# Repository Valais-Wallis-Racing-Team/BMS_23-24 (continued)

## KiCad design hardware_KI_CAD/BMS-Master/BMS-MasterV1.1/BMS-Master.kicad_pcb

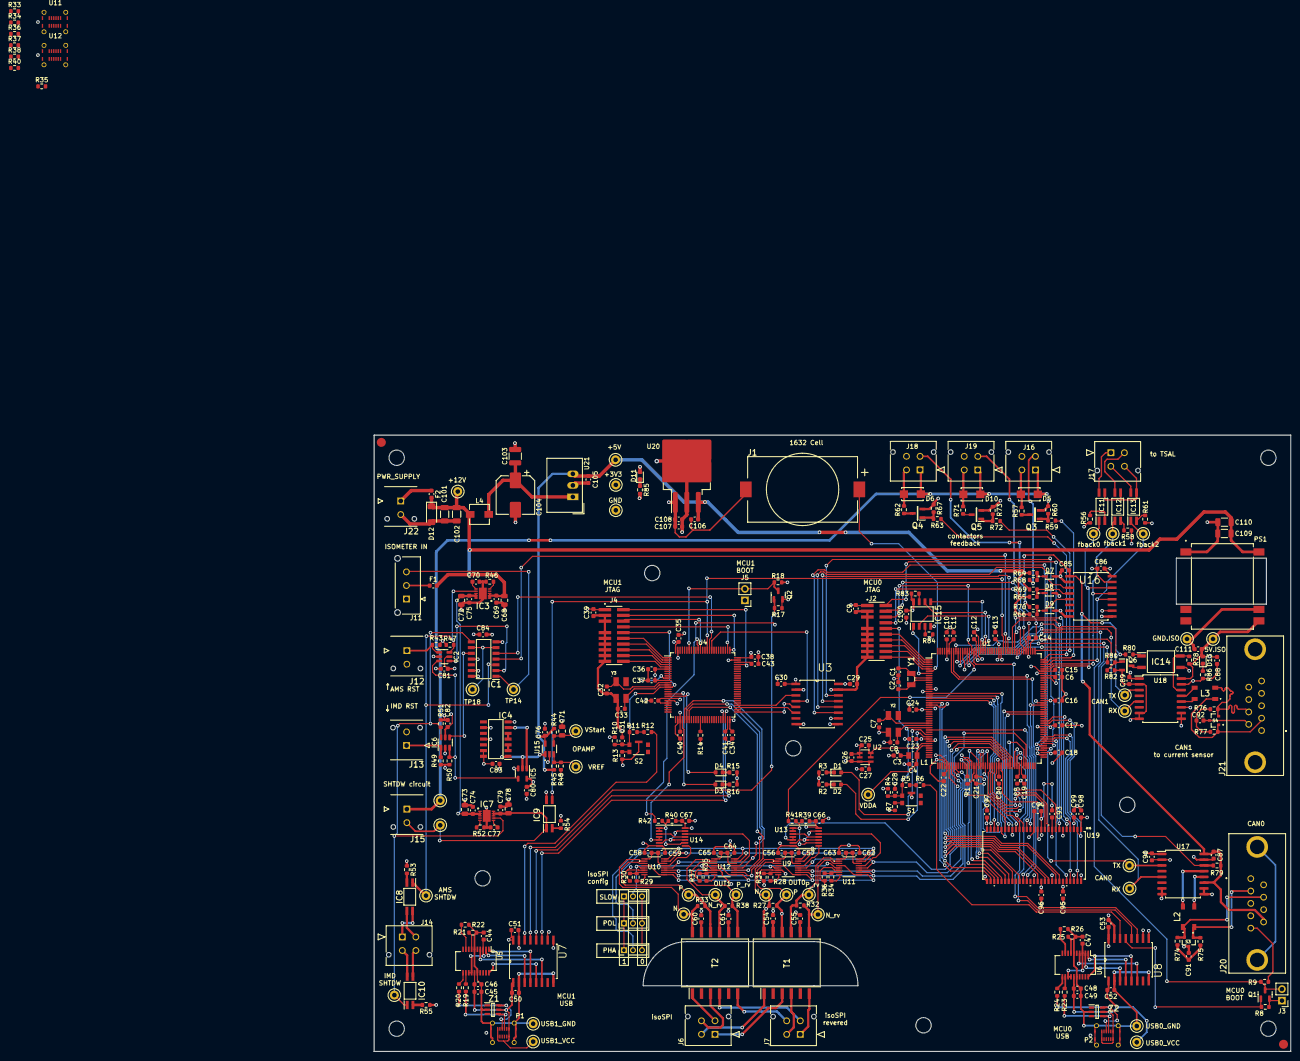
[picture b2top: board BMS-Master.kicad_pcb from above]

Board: 4 copper layers, 202.7 x 136.3 mm, 339 parts (0 on the bottom side), 274 nets.

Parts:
C1, C2, C7, C8, C32, C33: 18pF/50V; C_0603_1608Metric
C3, C4, C9, C10, C11, C12, C13, C14, C15, C16, C17, C18, C19, C20, C21, C22, C23, C24, C25, C27, C28, C29, C30, C31, C34, C35, C36, C37, C38, C39, C40, C42, C70, C77, C85, C86, C87, C88, C89, C90, C105, C106, C108, C111: 100nF/50V; C_0603_1608Metric
C5, C6, C41, C43: 2u2/10V; C_0603_1608Metric
C26, C91, C92, C107: 1uF/35V; C_0603_1608Metric
C44, C46, C47, C49, C50, C51, C52, C53, C56, C57, C58, C59, C62, C63, C64, C65, C66, C67, C76, C80, C81, C82, C83, C84, C93, C94, C95, C96, C97, C98, C99, C100: 100n/50V; C_0603_1608Metric
C45, C48: 4u7/25V; C_0603_1608Metric
C54, C55, C60, C61: 27pF/50V; C_0603_1608Metric
C68, C72, C73, C78: 10u/50V; C_0805_2012Metric
C69, C74, C75, C79: 0.1u/50V; C_0603_1608Metric
C71: 6.8uF/50V; C_0805_2012Metric
C101, C102: 10uF/50V; C_1206_3216Metric
C103: 10uF/50V; C_1210_3225Metric
C104: 56uF/50V; CP_Elec_8x10
C109, C110: 47uF/25V; C_1206_3216Metric
D1, D3: LED_RED; LED_0603_1608Metric
D2, D4: LED_Green; LED_0603_1608Metric
D5, D6, D10: GF1B-E3_67A; Diode_GF1B-E367A
D7, D8, D9: CDSOD323-T05; Bourns_Inc.-SOD-323-0-0-IPC_B
D11, D13: LED orange; LED_0603_1608Metric
D12: BZV55B15; D_MiniMELF
F1: 0408002.WR; Fuse_0603_1608Metric
F2: 0408007.WR; Fuse_0603_1608Metric
FID1, FID2: Fiducial; fiducial 2mm with 3mm mask
IC1: SN74LVC08AD; SOIC127P600X175-14N
IC2, IC6: SN74LVC1G332DBVR; TSOT-23-6
IC3, IC7: LS1205EF; SON50P300X300X80-11N
IC4: SN74HC04DR; SOIC127P600X175-14N
IC5: SN74LVC1G02DBVT; TSOT-23-5
IC8, IC9, IC10, IC11, IC12, IC13: ACPL-217-56BE; SOIC127P700X242-4N
IC14: AQY-211EHA; SOP254P962X315-4N
IC15: M95M02-DRMN6TP; SOIC127P600X175-8N
J1: SMTU1632-LF.TR; SMTU1632LFTR
J2, J4: FTSH-110-01-L-DV-007; SAMTEC_FTSH-110-01-L-DV-007
J3, J5: Conn_01x02_Pin; PinHeader_1x02_P2.54mm_Vertical
J6, J7, J14, J16, J17, J18, J19: 430450412; CON_430450412_MOL
J8, J9, J10: Conn_01x03_Pin; PinHeader_1x03_P2.00mm_Vertical
J11: 436500327; MOLEX_436500327
J12, J13, J15, J22: 43045-0212; 43045-02YY_121314
J20, J21: DE9_Receptacle_MountingHoles; L177TSEH09SOL2RM8
L1: BLM21AG471SN1J; IND_BLM21_0805_MUR
L2, L3: ACT45B 2000uH; ACT45B1012PTL003
L4: 5.6uH; L_TracoPower_TCK-141
P1, P2: USB_C_Plug_USB2.0; molex 2193200001
PS1: TRI_1-1211SM; CONV_TRI_1-1211SM
Q1, Q2: BSS84; SOT-23
Q3, Q4, Q5, Q6: IRLML0100TRPBF; SOT95P237X112-3N
R1, R4, R8, R9, R10, R14, R17, R18, R35#2, R43, R47, R48, R49, R50, R51, R60, R64, R65, R66, R67, R73, R78, R79, R82, R83, R84: 10k; R_0603_1608Metric
R2, R3, R15, R16, R53, R55, R56, R58, R61, R85: 130R; R_0603_1608Metric
R5, R11: 680R; R_0603_1608Metric
R6, R7, R12, R13, R21, R22, R25, R26, R33#2, R41, R42: 0R; R_0603_1608Metric
R19, R20, R23, R24: 27R; R_0603_1608Metric
R27, R32, R33, R38: 120R; R_0603_1608Metric
R28, R29, R34#2, R35: 820R; R_0603_1608Metric
R30, R31, R36#2, R37#2: 1k2; R_0603_1608Metric
R34, R39, R40#2: 20k; R_0603_1608Metric
R36, R37, R38#2, R40: 2k2; R_0603_1608Metric
R44: 100k; R_0603_1608Metric
R45, R57, R62, R71: 1k; R_0603_1608Metric
R46, R52: 6k8; R_0603_1608Metric
R54: 470R; R_0603_1608Metric
R59, R63, R72, R81: 10R; R_0603_1608Metric
R68, R69, R70: 47R; R_0603_1608Metric
R74, R75, R76, R77: 62R; R_0603_1608Metric
R80: 2k7; R_0603_1608Metric
R86: 200R; R_0603_1608Metric
S1, S2: KMR221GLFS; SW_KMR221GLFS
S3, S4: PESD1CAN_215; DIO_PESD1CAN_215
T1, T2: HM2102NL; SOP200P1473X500-12N
TP1, TP2, TP3, TP4, TP5, TP6, TP7, TP8, TP9, TP10, TP11, TP12, TP13, TP14, TP16, TP17, TP18, TP20, TP21, TP22, TP23, TP24, TP25, TP26, TP27, TP28, TP29, TP30, TP31, TP32, TP33, TP34, TP35, TP36: TestPoint; TestPoint_Keystone_5000-5004_Miniature
U1: STM32F429IIT6; LQFP-176_24x24mm_P0.5mm
U2: ADR3425ARJZ-R2; RJ_6_ADI
U3, U7, U8: ADUM3401CRWZ; SOIC127P1032X265-16N
U4: STM32F429VITx; LQFP-100_14x14mm_P0.5mm
U5, U6: FT231XS-R; SSOP-20_3.9x8.7mm_P0.635mm
U9, U10, U11#2, U12#2: LTC6820HMS-PBF; MS_05-08-1669_ADI
U11, U12: molex 2193200001
U13, U14: SN74LVC00AQPWRQ1; TSSOP-14_4.4x5mm_P0.65mm
U15: AD8628ARTZ-R2; SOT95P280X145-5N
U16: ADUM3300CRWZ; SOIC127P1032X265-16N
U17, U18: TJA1052IT/5Y; SOIC-16W_7.5x10.3mm_P1.27mm
U19: IS42S16400J-7TLI; 54L_TSOP-2_400_ISI
U20: LM1085IS-3.3/NOPB; TO-263-3_TabPin2
U21: TSR_2-2450; Converter_DCDC_TRACO_TSR-1_THT
Y1: ABS07-32.768KHZ-T; ABS07
Y2, Y3: 7B-8.000MAAJ-T; OSCSC500X320X105-4N
Z1, Z2: IP4220CZ6,125; SOT95P275X110-6N

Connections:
+3.3V: C3.1, C9.1, C10.1, C11.1, C12.1, C13.1, C14.1, C15.1, C16.1, C17.1, C18.1, C19.1, C20.1, C21.1, C22.1, C23.1, C24.1, C26.1, C27.1, C29.2, C30.2, C34.1, C35.1, C36.1, C37.1, C38.1, C39.1, C40.1, C42.1, C51.2, C53.2, C56.1, C57.1, C58.1, C59.1, C66.1, C67.1, C80.1, C81.1, C82.1, C83.1, C84.1, C86.2, C89.2, C90.2, C93.1, C94.1, C95.1, C96.1, C97.1, C98.1, C99.1, C100.1, C107.1, C108.1, D11.2 (A), IC1.14 (VCC), IC2.5 (VCC), IC4.9, IC4.11, IC4.13, IC4.14 (VCC), IC5.5 (VCC), IC6.5 (VCC), IC9.4 (C), IC15.8 (VCC), J2.01, J3.1, J4.01, J5.1, J8.1, J9.1, J10.1, J12.2, J13.2, L1.2, Q1.2 (S), Q2.2 (S), R4.1, R8.1, R10.1, R17.1, R34.1, R36.1, R37.1, R38#2.1, R39.1, R40.1, R40#2.1, R83.1, R84.1, TP33.1, U1.15 (VDD), U1.23 (VDD), U1.36 (VDD), U1.49 (VDD), U1.62 (VDD), U1.72 (VDD), U1.82 (VDD), U1.91 (VDD), U1.103 (VDD), U1.114 (VDD), U1.127 (VDD), U1.136 (VDD), U1.149 (VDD), U1.159 (VDD), U1.171 (PDR_ON), U1.172 (VDD), U2.3 (ENABLE), U2.4 (VIN), U3.1 (VDD1), U3.10 (VE2), U3.16 (VDD2), U4.6 (VBAT), U4.11 (VDD), U4.19 (VDD), U4.21 (VREF+), U4.22 (VDDA), U4.28 (VDD), U4.50 (VDD), U4.75 (VDD), U4.100 (VDD), U7.10 (VE2), U7.16 (VDD2), U8.10 (VE2), U8.16 (VDD2), U9.1 (EN), U9.6 (VDDS), U9.9 (VDD), U9.12 (MSTR), U10.1 (EN), U10.6 (VDDS), U10.9 (VDD), U10.12 (MSTR), U11#2.1 (EN), U11#2.12 (MSTR), U12#2.1 (EN), U12#2.12 (MSTR), U13.14 (VCC), U14.14 (VCC), U16.10 (VE2), U16.16 (VDD2), U17.1 (VDD1), U18.1 (VDD1), U19.1 (VDD), U19.3 (VDDQ), U19.9 (VDDQ), U19.14 (VDD), U19.27 (VDD), U19.43 (VDDQ), U19.49 (VDDQ), U20.2 (VO)
+5V: C76.1, C85.2, C87.2, C105.1, C106.1, J20.9, R44.1, R45.1, R64.1, R65.1, R66.1, R80.1, TP32.1, U15.5, U16.1 (VDD1), U17.11 (VDD2), U17.16 (VDD2), U20.3 (VI), U21.3 (Vout)
+5V_ISO: C88.2, C111.1, D13.2 (A), J21.9, PS1.8 (+VOUT), R78.1, TP35.1, U18.11 (VDD2), U18.16 (VDD2)
/CAN0_interface/CAN0.RX: TP29.1, U1.163 (PB5), U17.5 (RXD)
/CAN0_interface/CAN0.TRANS_STBY_CTRL: R79.1, U1.141 (PC12), U17.14 (STB)
/CAN0_interface/CAN0.TX: TP27.1, U1.93 (PB13), U17.3 (TXD)
/CAN0_interface/CAN0_H: J20.7, L2.1, R74.1, S3.2
/CAN0_interface/CAN0_L: J20.2, L2.2, R75.1, S3.1
/CAN0_interface/CAN1.RX: TP30.1, U1.167 (PB8), U18.5 (RXD)
/CAN0_interface/CAN1.TRANS_STBY_CTRL: R81.2, U1.165 (PB7)
/CAN0_interface/CAN1.TX: TP28.1, U1.168 (PB9), U18.3 (TXD)
/CAN0_interface/CAN1_+: J21.7, L3.2, R76.1, S4.2
/CAN0_interface/CAN1_-: J21.2, L3.1, R77.1, S4.1
/Contactors/Contactor_ctrl0: R59.1, U1.131 (PI0)
/Contactors/Contactor_ctrl1: R63.1, U1.132 (PI1)
/Contactors/Contactor_ctrl2: R72.1, U1.133 (PI2)
/Contactors/Contactor_feedback0: IC11.1 (A), TP24.1, U1.128 (PH13), U16.14 (VOA)
/Contactors/Contactor_feedback1: IC12.1 (A), TP25.1, U1.129 (PH14), U16.13 (VOB)
/Contactors/Contactor_feedback2: IC13.1 (A), TP26.1, U1.130 (PH15), U16.12 (VOC)
/Contactors/Contactor_out0: D5.2 (ANODE), J16.2, Q3.3 (D), R57.1
/Contactors/Contactor_out1: D6.2 (ANODE), J18.2, Q4.3 (D), R62.1
/Contactors/Contactor_out2: D10.2 (ANODE), J19.2, Q5.3 (D), R71.1
/Contactors/contactors_com_pos: D5.1 (CATHODE), D6.1 (CATHODE), D10.1 (CATHODE), J15.1, J16.1, J18.1, J19.1, TP23.1
/Contactors/feedback0: J16.3, R68.1
/Contactors/feedback1: J18.3, R69.1
/Contactors/feedback2: J19.3, R70.1
/MCU0_Memory/EEPROM.CS: IC15.1 (~S), U1.7 (PI8)
/MCU0_Memory/EEPROM.MISO: IC15.2 (Q), U1.155 (PG12)
/MCU0_Memory/EEPROM.MOSI: IC15.5 (D), U1.157 (PG14)
/MCU0_Memory/EEPROM.SCK: IC15.6 (C), U1.156 (PG13)
/MCU0_Memory/MCU0_RAM.A0: U1.16 (PF0), U19.23 (A0)
/MCU0_Memory/MCU0_RAM.A1: U1.17 (PF1), U19.24 (A1)
/MCU0_Memory/MCU0_RAM.A2: U1.18 (PF2), U19.25 (A2)
/MCU0_Memory/MCU0_RAM.A3: U1.19 (PF3), U19.26 (A3)
/MCU0_Memory/MCU0_RAM.A4: U1.20 (PF4), U19.29 (A4)
/MCU0_Memory/MCU0_RAM.A5: U1.21 (PF5), U19.30 (A5)
/MCU0_Memory/MCU0_RAM.A6: U1.60 (PF12), U19.31 (A6)
/MCU0_Memory/MCU0_RAM.A7: U1.63 (PF13), U19.32 (A7)
/MCU0_Memory/MCU0_RAM.A8: U1.64 (PF14), U19.33 (A8)
/MCU0_Memory/MCU0_RAM.A9: U1.65 (PF15), U19.34 (A9)
/MCU0_Memory/MCU0_RAM.A10: U1.66 (PG0), U19.22 (A10)
/MCU0_Memory/MCU0_RAM.A11: U1.67 (PG1), U19.35 (A11)
/MCU0_Memory/MCU0_RAM.BA0: U1.108 (PG4), U19.20 (BA0)
/MCU0_Memory/MCU0_RAM.BA1: U1.109 (PG5), U19.21 (BA1)
/MCU0_Memory/MCU0_RAM.D0: U1.104 (PD14), U19.2 (DQ0)
/MCU0_Memory/MCU0_RAM.D1: U1.105 (PD15), U19.4 (DQ1)
/MCU0_Memory/MCU0_RAM.D2: U1.142 (PD0), U19.5 (DQ2)
/MCU0_Memory/MCU0_RAM.D3: U1.143 (PD1), U19.7 (DQ3)
/MCU0_Memory/MCU0_RAM.D4: U1.68 (PE7), U19.8 (DQ4)
/MCU0_Memory/MCU0_RAM.D5: U1.69 (PE8), U19.10 (DQ5)
/MCU0_Memory/MCU0_RAM.D6: U1.70 (PE9), U19.11 (DQ6)
/MCU0_Memory/MCU0_RAM.D7: U1.73 (PE10), U19.13 (DQ7)
/MCU0_Memory/MCU0_RAM.D8: U1.74 (PE11), U19.42 (DQ8)
/MCU0_Memory/MCU0_RAM.D9: U1.75 (PE12), U19.44 (DQ9)
/MCU0_Memory/MCU0_RAM.D10: U1.76 (PE13), U19.45 (DQ10)
/MCU0_Memory/MCU0_RAM.D11: U1.77 (PE14), U19.47 (DQ11)
/MCU0_Memory/MCU0_RAM.D12: U1.78 (PE15), U19.48 (DQ12)
/MCU0_Memory/MCU0_RAM.D13: U1.96 (PD8), U19.50 (DQ13)
/MCU0_Memory/MCU0_RAM.D14: U1.97 (PD9), U19.51 (DQ14)
/MCU0_Memory/MCU0_RAM.D15: U1.98 (PD10), U19.53 (DQ15)
/MCU0_Memory/MCU0_RAM.NBL0: U1.169 (PE0), U19.15 (LDQM)
/MCU0_Memory/MCU0_RAM.NBL1: U1.170 (PE1), U19.39 (UDQM)
/MCU0_Memory/MCU0_RAM.SDCKE1: U1.84 (PH7), U19.37 (CKE)
/MCU0_Memory/MCU0_RAM.SDCLK: U1.112 (PG8), U19.38 (CLK)
/MCU0_Memory/MCU0_RAM.SDNCAS: U1.160 (PG15), U19.17 (CAS)
/MCU0_Memory/MCU0_RAM.SDNE1: U1.83 (PH6), U19.19 (CS)
/MCU0_Memory/MCU0_RAM.SDNRAS: U1.59 (PF11), U19.18 (RAS)
/MCU0_Memory/MCU0_RAM.SDNWE: U1.32 (PC0), U19.16 (WE)
/MCU0_primary/FTDI_MCU0.DTR: Q1.1 (G), R8.2, U8.13 (VOB)
/MCU0_primary/FTDI_MCU0.RTS: R6.2, U8.14 (VOA)
/MCU0_primary/FTDI_MCU0.RX: U1.80 (PB11), U8.12 (VOC)
/MCU0_primary/FTDI_MCU0.TX: U1.79 (PB10), U8.11 (VID)
/MCU0_primary/MCU0_ADC_REF/VREF+_MCU0: C25.1, U1.38 (VREF+), U2.5 (VOUTSENSE), U2.6 (VOUTFORCE)
/MCU0_primary/MCU0_BOOT: J3.2, Q1.3 (D), R9.1, U1.166 (BOOT0)
/MCU0_primary/MCU0_NRST: C28.1, J2.10, R4.2, R5.1, S1.1, U1.31 (NRST)
/MCU0_primary/MCU0_SWCLK: J2.04, U1.137 (PA14)
/MCU0_primary/MCU0_SWDIO: J2.02, U1.124 (PA13)
/MCU0_primary/MCU0_SWO: J2.06, U1.161 (PB3)
/MCU0_primary/MCU0_TDI: J2.08, U1.138 (PA15)
/MCU0_primary/MCU0_TRACECLK: J2.12, U1.1 (PE2)
/MCU0_primary/MCU0_TRACED0: J2.14, U1.2 (PE3)
/MCU0_primary/MCU0_TRACED1: J2.16, U1.3 (PE4)
/MCU0_primary/MCU0_TRACED2: J2.18, U1.4 (PE5)
/MCU0_primary/MCU0_TRACED3: J2.20, U1.5 (PE6)
/MCU0_primary/MCU_to_MCU_INTERFACE_MCU0.CS: U1.92 (PB12), U3.12 (VOC)
/MCU0_primary/MCU_to_MCU_INTERFACE_MCU0.MISO: U1.94 (PB14), U3.11 (VID)
/MCU0_primary/MCU_to_MCU_INTERFACE_MCU0.MOSI: U1.95 (PB15), U3.14 (VOA)
/MCU0_primary/MCU_to_MCU_INTERFACE_MCU0.SCK: U1.145 (PD3), U3.13 (VOB)
/MCU0_primary/SHUTDOWN_ctrl_MCU0: IC1.4, U1.146 (PD4)
/MCU0_primary/SHUTDOWN_feedback_MCU0: IC9.3 (E), U1.147 (PD5), U4.86 (PD5)
/MCU0_primary/isoSPI0.CS: U1.50 (PA4), U13.1, U13.2
/MCU0_primary/isoSPI0.DIR: R33#2.1, R41.1, U1.162 (PB4)
/MCU0_primary/isoSPI0.MISO: R36.2, U1.52 (PA6), U9.3 (MISO), U11#2.3 (MISO)
/MCU0_primary/isoSPI0.MOSI: R37.2, U1.53 (PA7), U9.2 (MOSI), U11#2.2 (MOSI)
/MCU0_primary/isoSPI0.SCK: U1.51 (PA5), U9.4 (SCK), U11#2.4 (SCK)
/MCU1_secondary/FTDI_MCU1.DTR: Q2.1 (G), R17.2, U7.13 (VOB)
/MCU1_secondary/FTDI_MCU1.RTS: R12.2, U7.14 (VOA)
/MCU1_secondary/FTDI_MCU1.RX: U4.48 (PB11), U7.12 (VOC)
/MCU1_secondary/FTDI_MCU1.TX: U4.47 (PB10), U7.11 (VID)
/MCU1_secondary/MCU1_BOOT: J5.2, Q2.3 (D), R18.1, U4.94 (BOOT0)
/MCU1_secondary/MCU1_NRST: C31.1, J4.10, R10.2, R11.1, S2.1, U4.14 (NRST)
/MCU1_secondary/MCU1_SWCLK: J4.04, U4.76 (PA14)
/MCU1_secondary/MCU1_SWDIO: J4.02, U4.72 (PA13)
/MCU1_secondary/MCU1_SWO: J4.06, U4.89 (PB3)
/MCU1_secondary/MCU1_TDI: J4.08, U4.77 (PA15)
/MCU1_secondary/MCU1_TRACECLK: J4.12, U4.1 (PE2)
/MCU1_secondary/MCU1_TRACED0: J4.14, U4.2 (PE3)
/MCU1_secondary/MCU1_TRACED1: J4.16, U4.3 (PE4)
/MCU1_secondary/MCU1_TRACED2: J4.18, U4.4 (PE5)
/MCU1_secondary/MCU1_TRACED3: J4.20, U4.5 (PE6)
/MCU1_secondary/MCU_to_MCU_INTERFACE_MCU1.CS: U3.5 (VIC), U4.51 (PB12)
/MCU1_secondary/MCU_to_MCU_INTERFACE_MCU1.MISO: U3.6 (VOD), U4.53 (PB14)
/MCU1_secondary/MCU_to_MCU_INTERFACE_MCU1.MOSI: U3.3 (VIA), U4.54 (PB15)
/MCU1_secondary/MCU_to_MCU_INTERFACE_MCU1.SCK: U3.4 (VIB), U4.84 (PD3)
/MCU1_secondary/SHUTDOWN_ctrl_MCU0: IC1.5, U4.85 (PD4)
/MCU1_secondary/isoSPI1.CS: U4.29 (PA4), U13.4, U13.5, U14.4, U14.5
/MCU1_secondary/isoSPI1.DIR: R42.1, U4.90 (PB4)
/MCU1_secondary/isoSPI1.MISO: R40.2, U4.31 (PA6), U10.3 (MISO), U12#2.3 (MISO)
/MCU1_secondary/isoSPI1.MOSI: R38#2.2, U4.32 (PA7), U10.2 (MOSI), U12#2.2 (MOSI)
/MCU1_secondary/isoSPI1.SCK: U4.30 (PA5), U10.4 (SCK), U12#2.4 (SCK)
/Shutdown/AMS_SHTDW: IC1.3, IC2.6, IC3.7 (EN), IC8.1 (A), R47.2, TP20.1
/Shutdown/Bender_OK_EXT: IC1.1, J11.3, TP14.1
/Shutdown/IMD_SHTDW: IC1.8, IC6.6, IC7.7 (EN), IC10.1 (A), R51.2, TP21.1
/USB_interface/D0+: P2.A6 (D+), R24.1, U12.A6 (D+), U12.B6 (D+), Z2.6 (I/O_4)
/USB_interface/D0-: P2.A7 (D-), R23.1, U12.A7 (D-), U12.B7 (D-), Z2.4 (I/O_3)
/USB_interface/D1+: P1.A6 (D+), R20.1, U11.A6 (D+), U11.B6 (D+), Z1.6 (I/O_4)
/USB_interface/D1-: P1.A7 (D-), R19.1, U11.A7 (D-), U11.B7 (D-), Z1.4 (I/O_3)
/USB_interface/USB_MCU0.DTR: U6.1 (~DTR), U8.4 (VIB)
/USB_interface/USB_MCU0.RTS: U6.2 (~RTS), U8.3 (VIA)
/USB_interface/USB_MCU0.RX: U6.4 (RXD), U8.6 (VOD)
/USB_interface/USB_MCU0.TX: U6.20 (TXD), U8.5 (VIC)
/USB_interface/USB_MCU1.DTR: U5.1 (~DTR), U7.4 (VIB)
/USB_interface/USB_MCU1.RTS: U5.2 (~RTS), U7.3 (VIA)
/USB_interface/USB_MCU1.RX: U5.4 (RXD), U7.6 (VOD)
/USB_interface/USB_MCU1.TX: U5.20 (TXD), U7.5 (VIC)
/isoSPI_interface/CS0_F: U9.5 (*CS), U13.8
/isoSPI_interface/CS0_rv: U11#2.5 (*CS), U13.12
/isoSPI_interface/CS1_F: U10.5 (*CS), U14.8
/isoSPI_interface/CS1_rv: U12#2.5 (*CS), U14.12
/isoSPI_interface/OUT0_N: R27.1, T1.12 (SEC_6), TP7.1, U9.10 (IM)
/isoSPI_interface/OUT0_P: R27.2, T1.10 (SEC_4), TP6.1, U9.11 (IP)
/isoSPI_interface/OUT1_N: R32.1, R33.1, T1.7 (SEC_1), T2.12 (SEC_6), TP9.1, TP11.1, U10.10 (IM)
/isoSPI_interface/OUT1_N_rv: R38.2, T2.9 (SEC_3), TP12.1, U12#2.10 (IM)
/isoSPI_interface/OUT1_P: R32.2, R33.2, T1.9 (SEC_3), T2.10 (SEC_4), TP8.1, TP10.1, U10.11 (IP)
/isoSPI_interface/OUT1_P_rv: R38.1, T2.7 (SEC_1), TP13.1, U12#2.11 (IP)
/isoSPI_interface/PHA_0: J9.2, U11#2.8 (PHA), U12#2.8 (PHA)
/isoSPI_interface/POL_0: J8.2, U11#2.7 (POL), U12#2.7 (POL)
/isoSPI_interface/SLOW: J10.2, U11#2.13 (SLOW), U12#2.13 (SLOW)
GND: C1.2, C2.2, C3.2, C4.2, C5.2, C6.2, C7.2, C8.2, C9.2, C10.2, C11.2, C12.2, C13.2, C14.2, C15.2, C16.2, C17.2, C18.2, C19.2, C20.2, C21.2, C22.2, C23.2, C24.2, C25.2, C26.2, C27.2, C28.2, C29.1, C30.1, C31.2, C32.2, C33.2, C34.2, C35.2, C36.2, C37.2, C38.2, C39.2, C40.2, C41.2, C42.2, C43.2, C51.1, C53.1, C54.1, C55.1, C56.2, C57.2, C58.2, C59.2, C60.1, C61.1, C62.2, C63.2, C64.2, C65.2, C66.2, C67.2, C68.2, C69.2, C70.2, C71.2, C72.2, C73.2, C74.2, C75.2, C76.2, C77.2, C78.2, C79.2, C80.2, C81.2, C82.2, C83.2, C84.2, C85.1, C86.1, C87.1, C89.1, C90.1, C91.2, C93.2, C94.2, C95.2, C96.2, C97.2, C98.2, C99.2, C100.2, C101.2, C102.2, C103.2, C104.2, C105.2, C106.2, C107.2, C108.2, C109.2, C110.2, D7.2, D8.2, D9.2, D12.2 (A), IC1.7 (GND), IC1.11, IC1.13, IC2.2 (GND), IC3.11 (GND), IC4.7 (GND), IC5.3 (GND), IC6.2 (GND), IC7.11 (GND), IC15.4 (VSS), J1.2 (-), J2.03, J2.05, J2.09, J2.11, J2.13, J2.15, J2.17, J2.19, J4.03, J4.05, J4.09, J4.11, J4.13, J4.15, J4.17, J4.19, J8.3, J9.3, J10.3, J11.1, J16.4, J18.4, J19.4, J20.3, J20.5, J20.6, J22.2, PS1.1 (-VIN), Q3.2 (S), Q4.2 (S), Q5.2 (S), Q6.2 (S), R1.1, R2.2, R3.2, R7.2, R9.2, R13.2, R14.2, R15.2, R16.2, R18.2, R30.1, R31.1, R36#2.1, R37#2.1, R43.1, R46.2, R47.1, R48.2, R49.1, R50.1, R51.1, R52.2, R53.1, R54.1, R55.1, R56.1, R58.1, R60.2, R61.1, R67.2, R73.2, R79.2, R82.2, R85.2, S1.5, S2.5, S3.3, TP34.1, U1.14 (VSS), U1.22 (VSS), U1.37 (VSSA), U1.48 (BYPASS_REG), U1.61 (VSS), U1.71 (VSS), U1.90 (VSS), U1.102 (VSS), U1.113 (VSS), U1.126 (VSS), U1.135 (VSS), U1.148 (VSS), U1.158 (VSS), U2.1 (GNDFORCE), U2.2 (GNDSENSE), U3.2 (GND1_2), U3.8 (GND1), U3.9 (GND2_2), U3.15 (GND2), U4.10 (VSS), U4.20 (VSSA), U4.27 (VSS), U4.74 (VSS), U4.99 (VSS), U7.9 (GND2_2), U7.15 (GND2), U8.9 (GND2_2), U8.15 (GND2), U9.7 (POL), U9.8 (PHA), U9.13 (SLOW), U9.14 (GND), U10.7 (POL), U10.8 (PHA), U10.13 (SLOW), U10.14 (GND), U11#2.14 (GND), U12#2.14 (GND), U13.7 (GND), U14.7 (GND), U15.2, U16.2 (GND1_2), U16.8 (GND1), U16.9 (GND2_2), U16.15 (GND2), U17.2 (GND1), U17.7 (GND1), U17.8 (GND1), U17.9 (GND2), U17.10 (GND2), U17.15 (GND2), U18.2 (GND1), U18.7 (GND1), U18.8 (GND1), U19.6 (GNDQ), U19.12 (GNDQ), U19.28 (GND), U19.41 (GND), U19.46 (GNDQ), U19.52 (GNDQ), U19.54 (GND), U20.1 (GND), U21.2 (GND), Y2.2 (GND), Y3.2 (GND)
GND_ISO: C88.1, C92.2, C111.2, IC14.3 (D1), J21.0 (PAD), J21.3, J21.5, J21.6, PS1.9 (-VOUT), R35#2.2, R86.2, S4.3, TP36.1, U18.9 (GND2), U18.10 (GND2), U18.15 (GND2)
unnamed: C71.1, R44.2, TP16.1, U15.4
unnamed: C91.1, R74.2, R75.2
unnamed: C92.1, R76.2, R77.2
unnamed: D1.2 (A), U1.34 (PC2)
unnamed: D1.1 (K), R3.1
unnamed: D2.2 (A), U1.35 (PC3)
unnamed: D2.1 (K), R2.1
unnamed: D3.2 (A), U4.17 (PC2)
unnamed: D3.1 (K), R16.1
unnamed: D4.2 (A), U4.18 (PC3)
unnamed: D4.1 (K), R15.1
unnamed: D11.1 (K), R85.1
unnamed: D13.1 (K), R86.1
unnamed: F1.1, J11.2
unnamed: F2.1, J22.1
unnamed: IC1.2, IC2.4
unnamed: IC1.6, IC1.9, TP18.1
unnamed: IC1.10, IC6.4
unnamed: IC2.1, J12.1, R43.2
unnamed: IC2.3, IC5.4, IC6.3, R50.2
unnamed: IC3.5 (ILIM), R46.1
unnamed: C72.1, C73.1, C74.1, C75.1, IC3.8 (OUT_3), IC3.9 (OUT_2), IC3.10 (OUT_1), IC7.1 (IN_1), IC7.2 (IN_2), IC7.3 (IN_3)
unnamed: C70.1, IC3.6 (SS)
unnamed: IC4.1, IC5.2, U15.1
unnamed: IC4.2, IC4.3
unnamed: IC4.4, IC4.5
unnamed: IC4.6, IC5.1
unnamed: IC6.1, J13.1, R49.2
unnamed: IC7.5 (ILIM), R52.1
unnamed: C78.1, C79.1, IC7.8 (OUT_3), IC7.9 (OUT_2), IC7.10 (OUT_1), IC9.1 (A), J15.2, TP22.1
unnamed: C77.1, IC7.6 (SS)
unnamed: IC8.4 (C), J14.1
unnamed: IC8.3 (E), J14.2
unnamed: IC8.2 (K), R53.2
unnamed: IC9.2 (K), R54.2
unnamed: IC10.4 (C), J14.3
unnamed: IC10.3 (E), J14.4
unnamed: IC10.2 (K), R55.2
unnamed: IC11.4 (C), J17.1
unnamed: IC11.3 (E), IC12.3 (E), IC13.3 (E), J17.4
unnamed: IC11.2 (K), R56.2
unnamed: IC12.4 (C), J17.2
unnamed: IC12.2 (K), R58.2
unnamed: IC13.4 (C), J17.3
unnamed: IC13.2 (K), R61.2
unnamed: IC14.1 (A), R80.2
unnamed: IC14.4 (D2), R78.2
unnamed: IC14.2 (K), Q6.3 (D)
unnamed: IC15.7 (~HOLD), R83.2
unnamed: IC15.3 (~W), R84.2
unnamed: J1.1 (+), U1.6 (VBAT)
unnamed: Q3.1 (G), R59.2, R60.1
unnamed: Q4.1 (G), R63.2, R67.1
unnamed: Q5.1 (G), R72.2, R73.1
unnamed: Q6.1 (G), R81.1, R82.1
unnamed: R5.2, R6.1
unnamed: R7.1, S1.2
unnamed: R11.2, R12.1
unnamed: R13.1, S2.2
unnamed: R33#2.2, R34.2, U13.11
unnamed: R39.2, R41.2, U13.9
unnamed: R40#2.2, R42.2, U14.1, U14.2, U14.9
unnamed: R45.2, R48.1, TP17.1, U15.3
unnamed: J6.2, T1.1 (PRI_1)
unnamed: J6.1, T1.3 (PRI_3)
unnamed: J6.3, J7.2, T1.4 (PRI_4)
unnamed: J6.4, J7.1, T1.6 (PRI_6)
unnamed: C55.2, T1.8 (SEC_2)
unnamed: C54.2, T1.11 (SEC_5)
unnamed: J7.3, T2.4 (PRI_4)
unnamed: J7.4, T2.6 (PRI_6)
unnamed: C61.2, T2.8 (SEC_2)
unnamed: C60.2, T2.11 (SEC_5)
unnamed: R1.2, U1.58 (PB2)
unnamed: C1.1, U1.9 (PC14), Y1.1
unnamed: C2.1, U1.10 (PC15), Y1.2
unnamed: C7.1, U1.29 (PH0), Y2.1
unnamed: C8.1, U1.30 (PH1), Y2.3 (2)
unnamed: C5.1, U1.81 (VCAP_1)
unnamed: C6.1, U1.125 (VCAP_2)
unnamed: C4.1, L1.1, TP1.1, U1.39 (VDDA)
unnamed: R14.1, U4.37 (PB2)
unnamed: C32.1, U4.12 (PH0), Y3.1
unnamed: C33.1, U4.13 (PH1), Y3.3 (2)
unnamed: C41.1, U4.49 (VCAP_1)
unnamed: C43.1, U4.73 (VCAP_2)
unnamed: C44.1, U5.3 (VCCIO), U5.13 (3V3OUT), U5.14 (~RESET)
unnamed: R19.2, U5.12 (USBDM)
unnamed: R20.2, U5.11 (USBDP)
unnamed: R22.1, U5.9 (~CTS)
unnamed: R21.1, U5.7 (~DSR)
unnamed: C47.1, U6.3 (VCCIO), U6.13 (3V3OUT), U6.14 (~RESET)
unnamed: R23.2, U6.12 (USBDM)
unnamed: R24.2, U6.11 (USBDP)
unnamed: R26.1, U6.9 (~CTS)
unnamed: R25.1, U6.7 (~DSR)
unnamed: R28.1, U9.16 (IBIAS)
unnamed: R28.2, R31.2, U9.15 (ICMP)
unnamed: R29.1, U10.16 (IBIAS)
unnamed: R29.2, R30.2, U10.15 (ICMP)
unnamed: R34#2.1, U11#2.16 (IBIAS)
unnamed: R34#2.2, R36#2.2, U11#2.15 (ICMP)
unnamed: C62.1, C63.1, U11#2.6 (VDDS), U11#2.9 (VDD)
unnamed: R35.1, U12#2.16 (IBIAS)
unnamed: R35.2, R37#2.2, U12#2.15 (ICMP)
unnamed: C64.1, C65.1, U12#2.6 (VDDS), U12#2.9 (VDD)
unnamed: U13.3, U13.10
unnamed: U13.6, U13.13
unnamed: U14.6, U14.10, U14.13
unnamed: U14.3, U14.11
unnamed: D7.1, R64.2, R68.2, U16.3 (VIA)
unnamed: D8.1, R65.2, R69.2, U16.4 (VIB)
unnamed: D9.1, R66.2, R70.2, U16.5 (VIC)
unnamed: L2.4, U17.13 (CANH)
unnamed: L2.3, U17.12 (CANL)
unnamed: L3.3, U18.13 (CANH)
unnamed: L3.4, U18.12 (CANL)
unnamed: R35#2.1, U18.14 (STB)
unnamed: C103.1, C104.1, L4.2, U21.1 (Vin)
SUPPLY: C68.1, C69.1, C101.1, C102.1, C109.1, C110.1, D12.1 (K), F1.2, F2.2, IC3.1 (IN_1), IC3.2 (IN_2), IC3.3 (IN_3), L4.1, PS1.14 (+VIN), TP31.1
USB0_GND: C47.2, C48.2, C49.2, C52.1, P2.A1 (GND), P2.A12 (GND), P2.B1 (GND), P2.B12 (GND), P2.S1 (SHIELD), R25.2, R26.2, TP4.1, U6.6 (GND), U6.16 (GND), U8.2 (GND1_2), U8.8 (GND1), U12.A1 (GND), U12.A12 (GND), U12.B1 (GND), U12.B12 (GND), U12.S1 (SHIELD), Z2.2 (GND)
USB1_GND: C44.2, C45.2, C46.2, C50.1, P1.A1 (GND), P1.A12 (GND), P1.B1 (GND), P1.B12 (GND), P1.S1 (SHIELD), R21.2, R22.2, TP3.1, U5.6 (GND), U5.16 (GND), U7.2 (GND1_2), U7.8 (GND1), U11.A1 (GND), U11.A12 (GND), U11.B1 (GND), U11.B12 (GND), U11.S1 (SHIELD), Z1.2 (GND)
USB1_VCC: C45.1, C46.1, C50.2, P1.A4 (VBUS), P1.A9 (VBUS), P1.B4 (VBUS), P1.B9 (VBUS), TP2.1, U5.15 (VCC), U7.1 (VDD1), U11.A4 (VBUS), U11.A9 (VBUS), U11.B4 (VBUS), U11.B9 (VBUS), Z1.5 (VP)
USB_VCC: C48.1, C49.1, C52.2, P2.A4 (VBUS), P2.A9 (VBUS), P2.B4 (VBUS), P2.B9 (VBUS), TP5.1, U6.15 (VCC), U8.1 (VDD1), U12.A4 (VBUS), U12.A9 (VBUS), U12.B4 (VBUS), U12.B9 (VBUS), Z2.5 (VP)

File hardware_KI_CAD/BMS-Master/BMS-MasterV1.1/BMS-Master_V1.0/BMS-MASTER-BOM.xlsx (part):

Fournisseur | Nbr. | N° article | Référence | Valeur | Empreinte | Description | Fitted (X) | Generic (X) | Through-hole (X) | prix unitaire | prix total
BOM BMS-Master |  |  |  |  |  |  |  |  |  | Liste actualisée le : 22.01.2024
Composants électriques et électroniques
 | 6 | generic | C1, C2, C7, C8, C32, C33 | 18pF/50V | 0603_1608Metric | capa 18pF/50V | x | x |  |  | 0
 | 44 | generic | C3, C4, C9-C25, C27-C31, C34-C40, C42, C70, C77, C85-C90, C105, C106, C108, C111 | 100nF/50V | 0603_1608Metric | capa 100nF/50V | x | x |  |  | 0
 | 4 | generic | C5, C6, C41, C43 | 2u2/10V | 0603_1608Metric | capa 2u2/10V | x | x |  |  | 0
 | 4 | generic | C26, C91, C92, C107 | 1uF/35V | 0603_1608Metric | capa 1uF/35V | x | x |  |  | 0
 | 32 | generic | C44, C46, C47, C49-C53, C56-C59, C62-C67, C76, C80-C84, C93-C100 | 100n/50V | 0603_1608Metric | capa 100nF/50V | x | x |  |  | 0
 | 2 | generic | C45, C48 | 4u7/25V | 0603_1608Metric | capa 4u7/25V | x | x |  |  | 0
 | 4 | generic | C54, C55, C60, C61 | 27pF/50V | 0603_1608Metric | capa 27pF/50V | x | x |  |  | 0
 | 4 | generic | C68, C72, C73, C78 | 10u/50V | 0805_2012Metric | capa10uF/50V | x | x |  |  | 0
 | 4 | generic | C69, C74, C75, C79 | 0.1u/50V | 0603_1608Metric | capa 0.1uF/50V | x | x |  |  | 0
 | 1 | generic | C71 | 68uF/50V | 0805_2012Metric | capa 68uF/50V | x | x |  |  | 0
 | 2 | generic | C101, C102 | 10uF/50V | 1206_3216Metric | capa 10uF/50V | x | x |  |  | 0
 | 1 | generic | C103 | 10uF/50V | 1210_3225Metric | capa 10uF/50V | x | x |  |  | 0
Mouser | 1 | 581-AEA0810560M050R | C104 | 56uF/50V | CP_Elec_8x10 | Aluminium Electrolytic Capacitors - SMD 50V 56pF 0810 20% | x |  |  | 0.66 | 0.66
 | 2 | generic | C109, C110 | 47uF/25V | C_1206_3216Metric | capa 47uF/25V | x | x |  |  | 0
Mouser | 2 | 78-TLMS1100-GS15 | D1, D3 | LED_RED | LED_0603_1608Metric | Standard LEDs - SMD CHIPLED(SMD 0603-LED) RED-E4 | x |  |  | 0.4 | 0.8
Mouser | 2 | 78-TLMG1100-GS15 | D2, D4 | LED_Green | LED_0603_1608Metric | Standard LEDs - SMD CHIPLED(SMD 0603-LED) GREEN U.BRIGHT-E4 | x |  |  | 0.4 | 0.8
Mouser | 3 | 625-GF1B-E3 | D5, D6, D10 | GF1B-E3_67A | GF1 (DO-214BA) | Rectifiers 1.0 Amp 100 Volt | x |  |  | 0.4 | 1.2000000000000002
Mouser | 3 | 652-CDSOD323-T05 | D7-D9 | CDSOD323-T05 | SOD-323 | ESD Suppressors / TVS Diodes TVS Diode 5VOLT | x |  |  | 0.53 | 1.59
Mouser | 2 | 78-TLMO1100-GS15 | D11, D13 | LED orange | LED_0603_1608Metric | Standard LEDs - SMD CHIPLED(SMD 0603-LED) S.ORANGE ULTRA-E4 | x |  |  | 0.4 | 0.8
Mouser | 1 | 771-BZV55-B15-T/R | D12 | BZV55B15 | MiniMELF | Zener Diodes BZV55-B15/SOD80/LLDS | x |  |  | 0.21 | 0.21
Mouser | 1 | 576-0408002.WR | F1 | 0408002.WR | Fuse_0603_1608Metric | Surface Mount Fuses FUSE 32V HIGH I2T 0603 TL 2A | x |  |  | 1.17 | 1.17
Mouser | 1 | 530-0ABB-7000-TM | F2 | 0408007.WR | Fuse_0603_1608Metric | Surface Mount Fuses 0603 SMD Fuse. Slow Blow 7A | x |  |  | 0.7 | 0.7
Mouser | 1 | 595-SN74LVC08AD | IC1 | SN74LVC08AD | SOIC-14 | Logic Gates Quad 2-Input AND | x |  |  | 0.86 | 0.86
Mouser | 2 | 595-SN74LVC1G332DBVR | IC2, IC6 | SN74LVC1G332DBVR | SOT-23-6 | Logic Gates Sngl 3 Inpt + OR Gt | x |  |  | 0.36 | 0.72
Mouser | 2 | 576-LS1205EFD33 | IC3, IC7 | LS1205EF | DFN3x3_10 | Power Switch ICs - Power Distribution 18V/5A efuse with OCP & Fault Indication | x |  |  | 1.3 | 2.6
Mouser | 1 | 595-SN74HC04DRG3 | IC4 | SN74HC04DR | SOIC-14 | Inverters Hex Inverters 6 gates | x |  |  | 0.48 | 0.48
Mouser | 1 | 595-SN74LVC1G02DBVT | IC5 | SN74LVC1G02DBVT | SOT-23-5 | Logic Gates SNGL 2 Input Pos NOR Gate | x |  |  | 0.61 | 0.61
Mouser | 6 | 630-ACPL-217-56BE | IC8-IC13 | ACPL-217-56BE | SO-4 | Transistor Output Optocouplers 3000Vrms 50% CTR | x |  |  | 0.59 | 3.54
Mouser | 1 | 769-AQY211EHA | IC14 | AQY-211EHA | SOP254P962X315-4N | Solid State Relays - PCB Mount 30v 1000mA DIP Form A Norm-Open | x |  |  | 2.72 | 2.72
Mouser | 1 | 511-M95M02-DRMN6TP | IC15 | M95M02-DRMN6TP | SOIC-8 | EEPROM 2 Mbit serial SPI 2Mb 5MHz EEPROM | x |  |  | 1.86 | 1.86
Mouser | 1 | 614-SMTU1632-LF.TR | J1 | SMTU1632-LF.TR | SMTU1632LFTR | Coin Cell Battery Holders SFC MNT FOR CR1632 520PCS/REEL | x |  |  | 1.67 | 1.67
Mouser | 2 | 200-FTSH11001LDV007 | J2, J4 | FTSH-110-01-L-DV-007 | SAMTEC_FTSH-110-01-L-DV-007 | High Reliability Header Strips, .050" pitch | x |  | x | 4.91 | 9.82
Mouser | 2 | 571-146280-2 | J3, J5 | Conn_01x02_Pin | PinHeader_1x02_P2.54mm_Vertical | 1x2 GPIO connector male | x |  | x | 0.38 | 0.76
Mouser | 7 | 538-43045-0412 | J6, J7, J14, J16-J19 | 430450412 | CON_430450412_MOL | Molex microfit 3.0 2x2 | x |  | x | 0.94 | 6.58
Mouser | 3 | 200-TMS10302GS | J8-J10 | Conn_01x03_Pin | PinHeader_1x03_P2.00mm_Vertical | 1x3 GPIO connector male | x |  | x | 0.57999999999999996 | 1.7399999999999998
Mouser | 1 | 538-43650-0327 | J11 | 436500327 | 43650-0327:MOLEX_436500327 | Molex microfit 3.0 1x3 | x |  | x | 1.05 | 1.05
Mouser | 4 | 538-430-45-0212 | J12, J13, J15, J22 | 43045-0212 | 43045-0212:43045-02YY_121314 | Molex microfit 3.0 1x2 | x |  | x | 0.75 | 3
Mouser | 2 | 523-TSEH09SOL2RM8 | J20, J21 | DE9_Receptacle_MountingHoles | L177TSEH09SOL2RM8 | D-Sub -9 Standard Connectors D-SUB | x |  | x | 1.73 | 3.46
Mouser | 1 | 81-BLM21AG471SN1D | L1 | BLM21AG471SN1J | IND_BLM21_0805_MUR | Ferrite Beads 470 OHM 25% Alternate Sizing Guide Below | x |  |  | 0.13 | 0.13
Mouser | 2 | 810-ACT45B5102PTL003 | L2, L3 | ACT45B 51uH | ACT45B1012PTL003 | Common Mode Chokes / Filters 2000ohms 51uH 200mA CAN-BUS AEC-Q200 150degC | x |  |  | 1.58 | 3.16
Mouser | 1 | 495-TCK-141 | L4 | 5.6uH | L_TracoPower_TCK-141 | Power Inductors - SMD EMC Chokes for DC/DC Converters | x |  |  | 5.78 | 5.78
Mouser | 2 | 538-219320-0001 | P1, P2 | USB_C_Plug_USB2.0 | molex 2193200001 | USB Connectors 16p Height 8.8mm (Type C) | x |  | x | 1.43 | 2.86
Mouser | 1 | 495-TRI1-1211SM | PS1 | TRI_1-1211SM | CONV_TRI_1-1211SM | Isolated DC/DC Converters - 1W 10.8-13.2Vin 5V 200mA SMD-14 | x |  |  | 14.47 | 14.47
Mouser | 2 | 512-BSS84 | Q1, Q2 | BSS84 | SOT-23-3 | MOSFET SOT-23 P-CH ENHANCE | x |  |  | 0.42 | 0.84
Mouser | 4 | 942-IRLML0100TRPBF | Q3-Q6 | IRLML0100TRPBF | SOT-23-3 | MOSFET N-CH 100V 1.6A 220mOhm 2.5nC Qg | x |  |  | 0.4 | 1.6
 | 26 | generic | R1, R4, R8-R10, R14, R17, R18, R43, R44, R47-R51, R60, R64-R67, R73, R78, R79, 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 | 10k | 0603_1608Metric | resistance 10k | x | x |  |  | 0
 | 4 | generic | R2, R3, R15, R16 | 130 | 0603_1608Metric | resistance 130R | x | x |  |  | 0
 | 2 | generic | R5, R11 | 680R | 0603_1608Metric | resistance 680R | x | x |  |  | 0
 | 10 | generic | R6, R7, R12, R13, R21, R22, R25, R26, R41, R42 | 0R | 0603_1608Metric | resistance 0R | x | x |  |  | 0
 | 4 | generic | R19, R20, R23, R24 | 27R | 0603_1608Metric | resistance 27R | x | x |  |  | 0
 | 4 | generic | R27, R32, R33, R38 | 120R | 0603_1608Metric | resistance 120R | x | x |  |  | 0
 | 4 | generic | R28, R29, R34, R35 | 820R | 0603_1608Metric | resistance 820R | x | x |  |  | 0
 | 4 | generic | R30, R31, R36, R37 | 1k2 | 0603_1608Metric | resistance 1k2 | x | x |  |  | 0
 | 2 | generic | R39, R40 | 20k | 0603_1608Metric | resistance 20k | x | x |  |  | 0
 | 4 | generic | R45, R57, R62, R71 | 1k | 0603_1608Metric | resistance 1k2 | x | x |  |  | 0
 | 2 | generic | R46, R52 | 6k8 | 0603_1608Metric | resistance 6k8 | x | x |  |  | 0
 | 6 | generic | R53, R55, R56, R58, R61, R85 | 130R | 0603_1608Metric | resistance 130R | x | x |  |  | 0
 | 1 | generic | R54 | 470R | 0603_1608Metric | resistance 470R | x | x |  |  | 0
 | 4 | generic | R59, R63, R72, R81 | 10R | 0603_1608Metric | resistance 10R | x | x |  |  | 0
 | 3 | generic | R68-R70 | 47R | 0603_1608Metric | resistance 47R | x | x |  |  | 0
 | 4 | generic | R74-R77 | 62R | 0603_1608Metric | resistance 62R | x | x |  |  | 0
 | 1 | generic | R80 | 2k7 | 0603_1608Metric | resistance 2k7 | x | x |  |  | 0
 | 1 | generic | R86 | 200R | 0603_1608Metric | resistance 200R | x | x |  |  | 0
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
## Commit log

2024-06-04 V1.0
2024-06-04 V1.1
2024-06-04 V1.2
2024-06-04 V1.3
2024-06-04 V1.4
2024-06-04 V1.5
2024-06-04 V1.6
2024-06-04 Beta
2024-06-04 Beta1
2024-06-05 V1.7_Beta
    longer wait for interlock to wait before checking state again
2024-06-08 V1.7 Beta 2
    added open wire periodic check, and can messages
2024-06-08 real V1.7 Beta 2 with 4 segment
2024-06-10 V1.7 Beta 3
    version at end of 2nd rolling try
    other commented out things for error ingnoring
2024-06-11 V1.7 Beta 4
    CRC and MUX errors do not put bms in error
2024-06-15 last test
2024-07-03 tous les messges s'envoient maintenant
    l'erreur vennais du temps avant d'envoyer le premier message qui doit etre inferieur du temps auquel l'on envoi le message periodiquement
2024-07-04 temps de delanhements ammeiloré
    en cas d'erreur les contacteurs s'ouvernt plus rapidement
2024-07-07 last version
    minor changes
2024-07-09 alpha 1
    all can messges are sent correctly
2024-07-10 not working
2024-07-10 capteur de courant fonctionne
2024-07-10 merging some changes from alpha
2024-07-10 some changes for error speeds
2024-07-10 new changes
    not working when driving and problem with crc error still here
2024-07-11 les contacteurs se ferment completement
    crc check +10 fois pour erreur correcte
2024-07-12 inbetween save
2024-07-29 version of the swiss competition
    save before i change things
2024-07-31 minor changes
    changed some balancing values
    changed so that default mode after bootup is standby instead of idle
2024-07-31 some updates since sleepless night
2024-07-31 minor changes
2024-08-07 changes with response time of diag and misculinous
    also changed that the open interlock requiers a standby message to be send before reclosing contactors after interlock is closed again
2024-08-09 rewoked some changes and changed
